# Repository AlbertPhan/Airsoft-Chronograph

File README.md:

# Airsoft-Chronograph
update: Prototype is working but not all features are done. Project isn't currently being worked on. You can take a look at my schematics and board and possibly build it yourself.

I am making an Airsoft Chronograph which uses 3D printed parts and an arduino nano as the brains. 
The chronograph will have multiple features such as:

Normalized fps (fps if it were a 0.20g bb)

Average fps

Rate of Fire

Min/Max FPS

Max deviation

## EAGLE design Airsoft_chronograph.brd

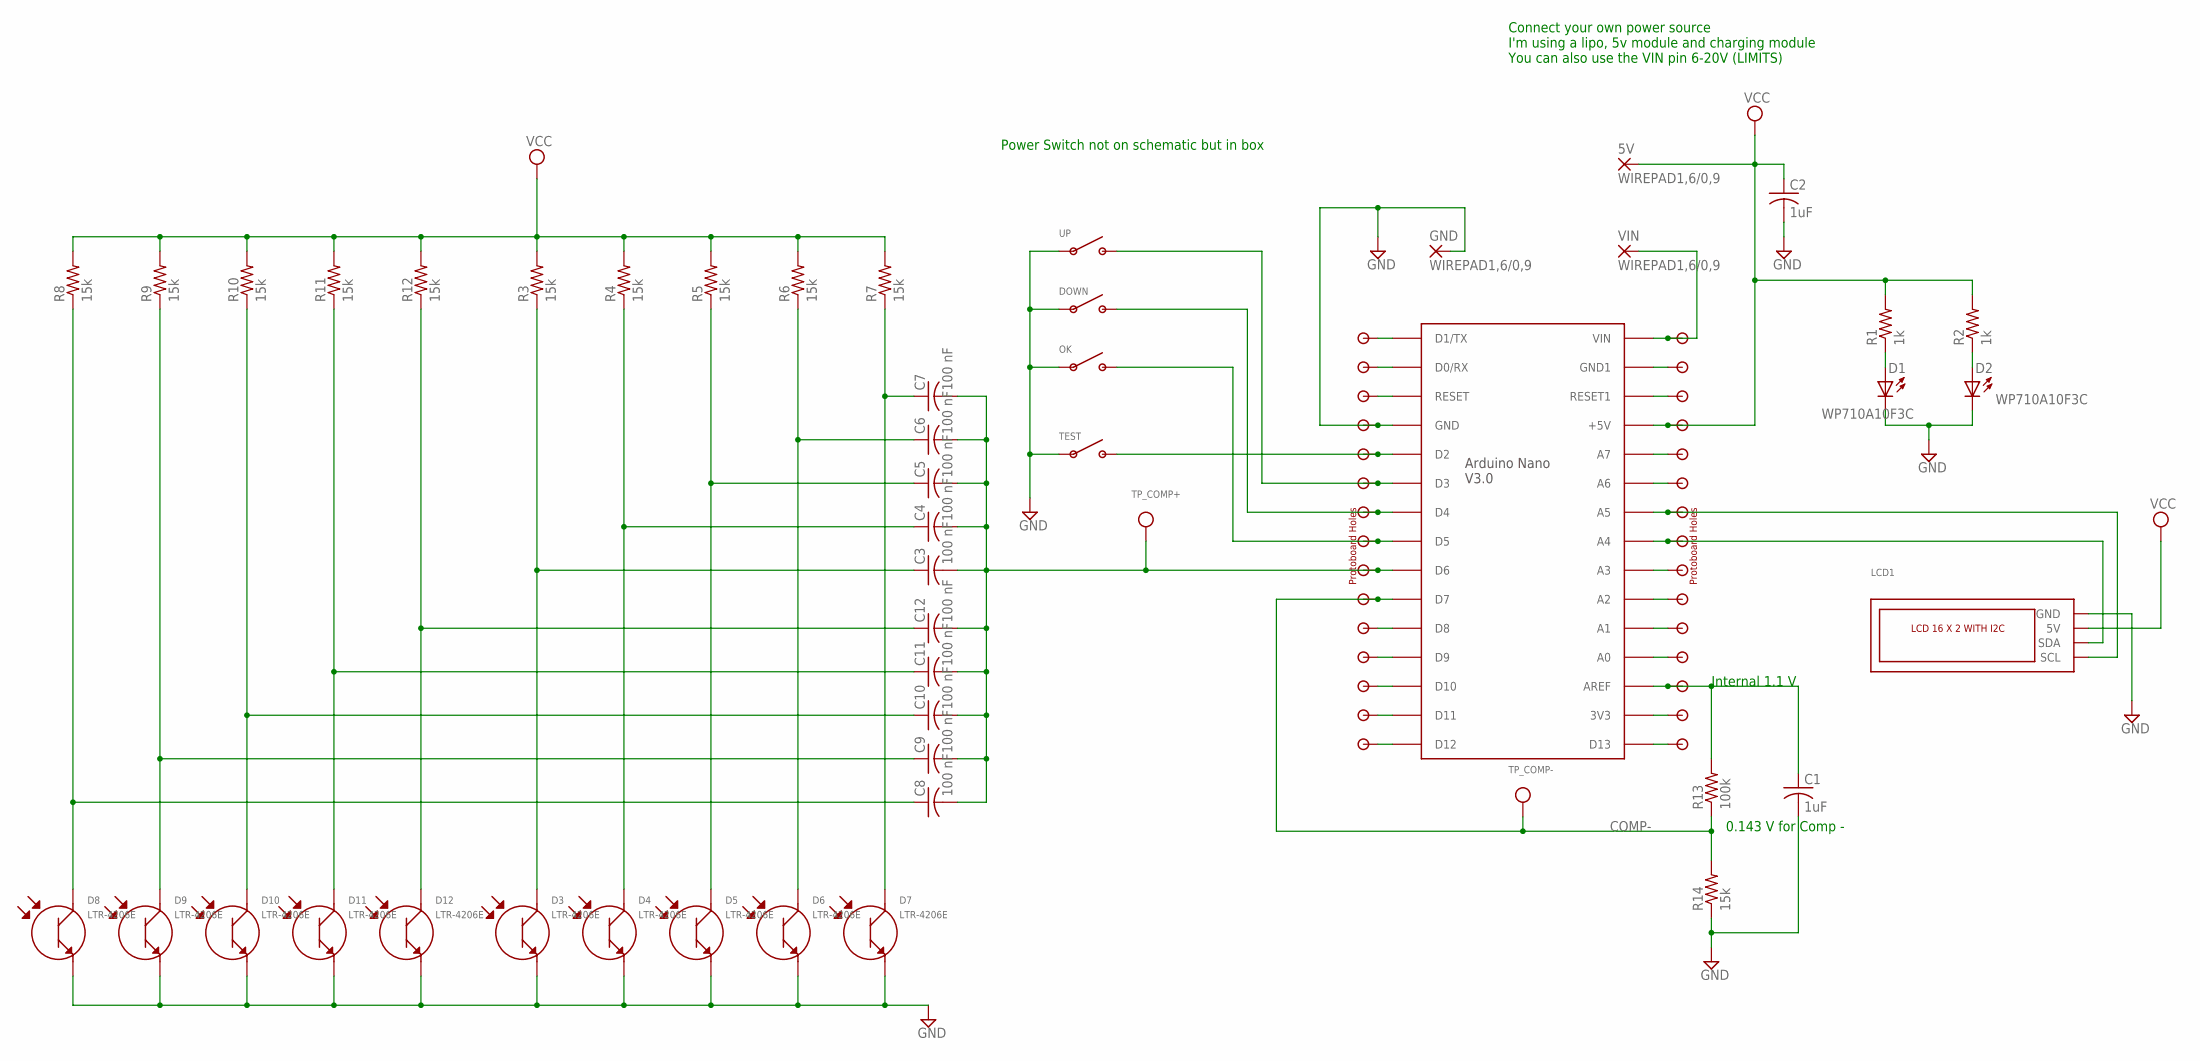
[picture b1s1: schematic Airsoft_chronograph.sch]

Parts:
5V: WIREPAD1,6/0,9; 1,6/0,9
C1, C2: 1uF; C0805
C3, C4, C5, C6, C7, C8, C9, C10, C11, C12: 100 nF; C0805
D1, D2: WP710A10F3C; 3MMLED
D3, D4, D5, D6, D7, D8, D9, D10, D11, D12: LTR-4206E; 3MMLED
DOWN: SW_SPST; 2WIRES
GND: WIREPAD1,6/0,9; 1,6/0,9
LCD1: LCD_16X2_I2C; LCD_I2C
OK: SW_SPST; 2WIRES
R1, R2: 1k; M0805
R3, R4, R5, R6, R7, R8, R9, R10, R11, R12, R14: 15k; M0805
R13: 100k; M0805
TEST: SW_SPST; 2WIRES
TP_COMP+: TESTPOINT0.1"; 1X01_ROUND
TP_COMP-: TESTPOINT0.1"; 1X01_ROUND
U$1: Arduino Nano V3; PDIP-32
U$2, U$3: 1X15_PROTO
UP: SW_SPST; 2WIRES
VIN: WIREPAD1,6/0,9; 1,6/0,9

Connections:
COMP-: R13.1, R14.2, TP_COMP-.1, U$1.D7, U$2.10
GND: C1.2, C2.2, D1.K, D2.K, D3.A (EMITTER+), D4.A (EMITTER+), D5.A (EMITTER+), D6.A (EMITTER+), D7.A (EMITTER+), D8.A (EMITTER+), D9.A (EMITTER+), D10.A (EMITTER+), D11.A (EMITTER+), D12.A (EMITTER+), DOWN.P$1 (A), GND.1, LCD1.GND, OK.P$1 (A), R14.1, TEST.P$1 (A), U$1.GND, U$2.4, UP.P$1 (A)
unnamed: D1.A, R1.1
unnamed: D2.A, R2.1
unnamed: C3.1, D3.K (COLLECTOR-), R3.1
unnamed: C4.1, D4.K (COLLECTOR-), R4.1
unnamed: C5.1, D5.K (COLLECTOR-), R5.1
unnamed: C6.1, D6.K (COLLECTOR-), R6.1
unnamed: C7.1, D7.K (COLLECTOR-), R7.1
unnamed: C8.1, D8.K (COLLECTOR-), R8.1
unnamed: C9.1, D9.K (COLLECTOR-), R9.1
unnamed: C10.1, D10.K (COLLECTOR-), R10.1
unnamed: C11.1, D11.K (COLLECTOR-), R11.1
unnamed: C12.1, D12.K (COLLECTOR-), R12.1
unnamed: C3.2, C4.2, C5.2, C6.2, C7.2, C8.2, C9.2, C10.2, C11.2, C12.2, TP_COMP+.1, U$1.D6, U$2.9
unnamed: U$1.D3, U$2.6, UP.P$2 (B)
unnamed: DOWN.P$2 (B), U$1.D4, U$2.7
unnamed: OK.P$2 (B), U$1.D5, U$2.8
unnamed: TEST.P$2 (B), U$1.D2, U$2.5
unnamed: LCD1.SDA, U$1.A4, U$3.8
unnamed: LCD1.SCL, U$1.A5, U$3.7
unnamed: U$1.D1/TX, U$2.1
unnamed: C1.1, R13.2, U$1.AREF, U$3.13
unnamed: U$1.D0/RX, U$2.2
unnamed: U$1.VIN, U$3.1, VIN.1
unnamed: U$1.RESET, U$2.3
unnamed: U$1.D8, U$2.11
unnamed: U$1.D9, U$2.12
unnamed: U$1.D10, U$2.13
unnamed: U$1.D11, U$2.14
unnamed: U$1.D12, U$2.15
unnamed: U$1.GND1, U$3.2
unnamed: U$1.RESET1, U$3.3
unnamed: U$1.A7, U$3.5
unnamed: U$1.A6, U$3.6
unnamed: U$1.A3, U$3.9
unnamed: U$1.A2, U$3.10
unnamed: U$1.A1, U$3.11
unnamed: U$1.A0, U$3.12
unnamed: U$1.3V3, U$3.14
unnamed: U$1.D13, U$3.15
VCC: 5V.1, C2.1, LCD1.5V, R1.2, R2.2, R3.2, R4.2, R5.2, R6.2, R7.2, R8.2, R9.2, R10.2, R11.2, R12.2, U$1.+5V, U$3.4

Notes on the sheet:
Internal 1.1 V
0.143 V for Comp -
Power Switch not on schematic but in box
Connect your own power source I'm using a lipo, 5v module and charging module You can also use the VIN pin 6-20V (LIMITS)

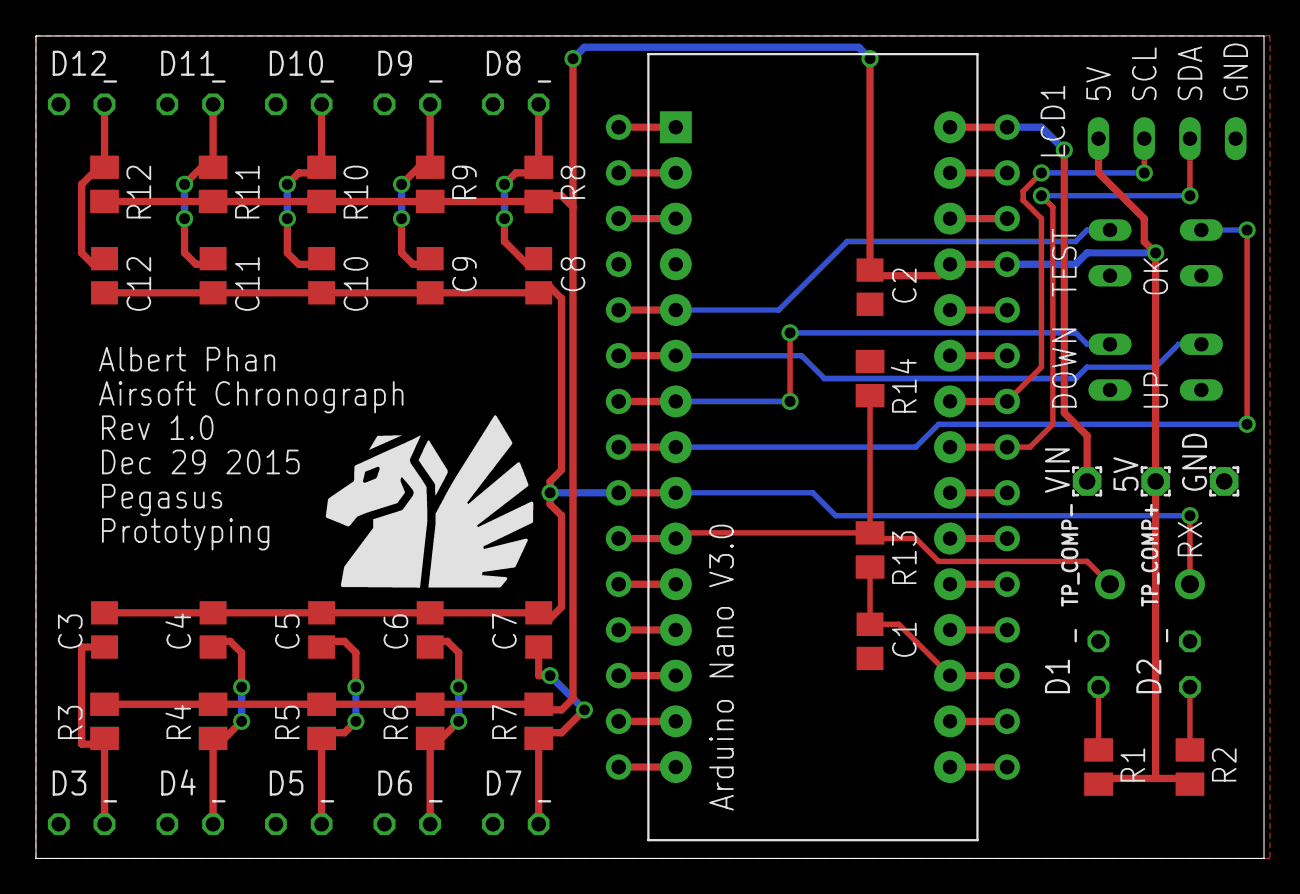
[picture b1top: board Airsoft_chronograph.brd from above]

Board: 2 copper layers, 68.2 x 45.7 mm, 51 parts (0 on the bottom side), 42 nets.

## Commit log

2015-03-26 :circus_tent: Added .gitattributes & .gitignore files
2015-03-26 Added some basic info
2015-03-26 Added Arduino Sketch File
    Buttons all work, LCD works. Normalized FPS menu completed with editing
    bbweight enabled. FPS is captured properly using the 2 sets of IR Beams.
    To be completed next: Averaging menu
2015-03-26 Ignored Visual Micro extra files
2015-03-28 Updated Averaging menu
    Did most of averaging menu. Clearing bbCount works, average display
    works. Ran into some problems with retrigger() not working. retrigger()
    works in the example from the library but not here. Very strange.
2015-03-28 Updated gitignore
2015-03-29 Finished Averaging and MINMAX menu
    Also added drawScreen() for easier reading. To do: Rate of fire code and
    menu.
2015-03-29 Fixed testBtn.retrigger()
    the retrigger didnt get a new fps
2015-03-29 Comment fix
2015-07-26 Added noise immunity to the comparator
    Made a check for minimum comparator output time
2015-07-26 Fixed bbcount over 99 not displaying
2015-08-08 Added Joules Menu
    Editing bbweight works in joules menu as well
2015-11-15 Completed ROF functionality
    ROF/ BPS menu complete, although BPS accuracy not exactly tested.
2015-12-30 Added Internal Ref for comparator
2016-10-20 Added Eagle schematic and board
    This was done back in 2015 but I never uploaded. Board has never been tested/made.
2016-10-20 Added libraries used in project

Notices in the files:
parts and their libraries:
microbuilder: This work is placed in the public domain, and may be freely used for commercial and non-commercial work with the following conditions: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
